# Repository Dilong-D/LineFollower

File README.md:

# LineFollower

Other materials used:

http://forbot.pl/blog/artykuly/podstawy/algorytm-linefollowera-c-poczatkujacych-id2722

http://forum.atnel.pl/topic7786.html

http://mikrokontroler.pl/page/3/?tag=kurs%20ATXmega

http://www.sunduino.pl/wordpress/xmega-adc-ogolnie-czesc-1/

https://extronic.pl/content/category/11-kurs-xmega

http://embedded-lab.com/blog/xmega-adc/

http://www.avrfreaks.net/forum/solved-xmega-all-adc-channels

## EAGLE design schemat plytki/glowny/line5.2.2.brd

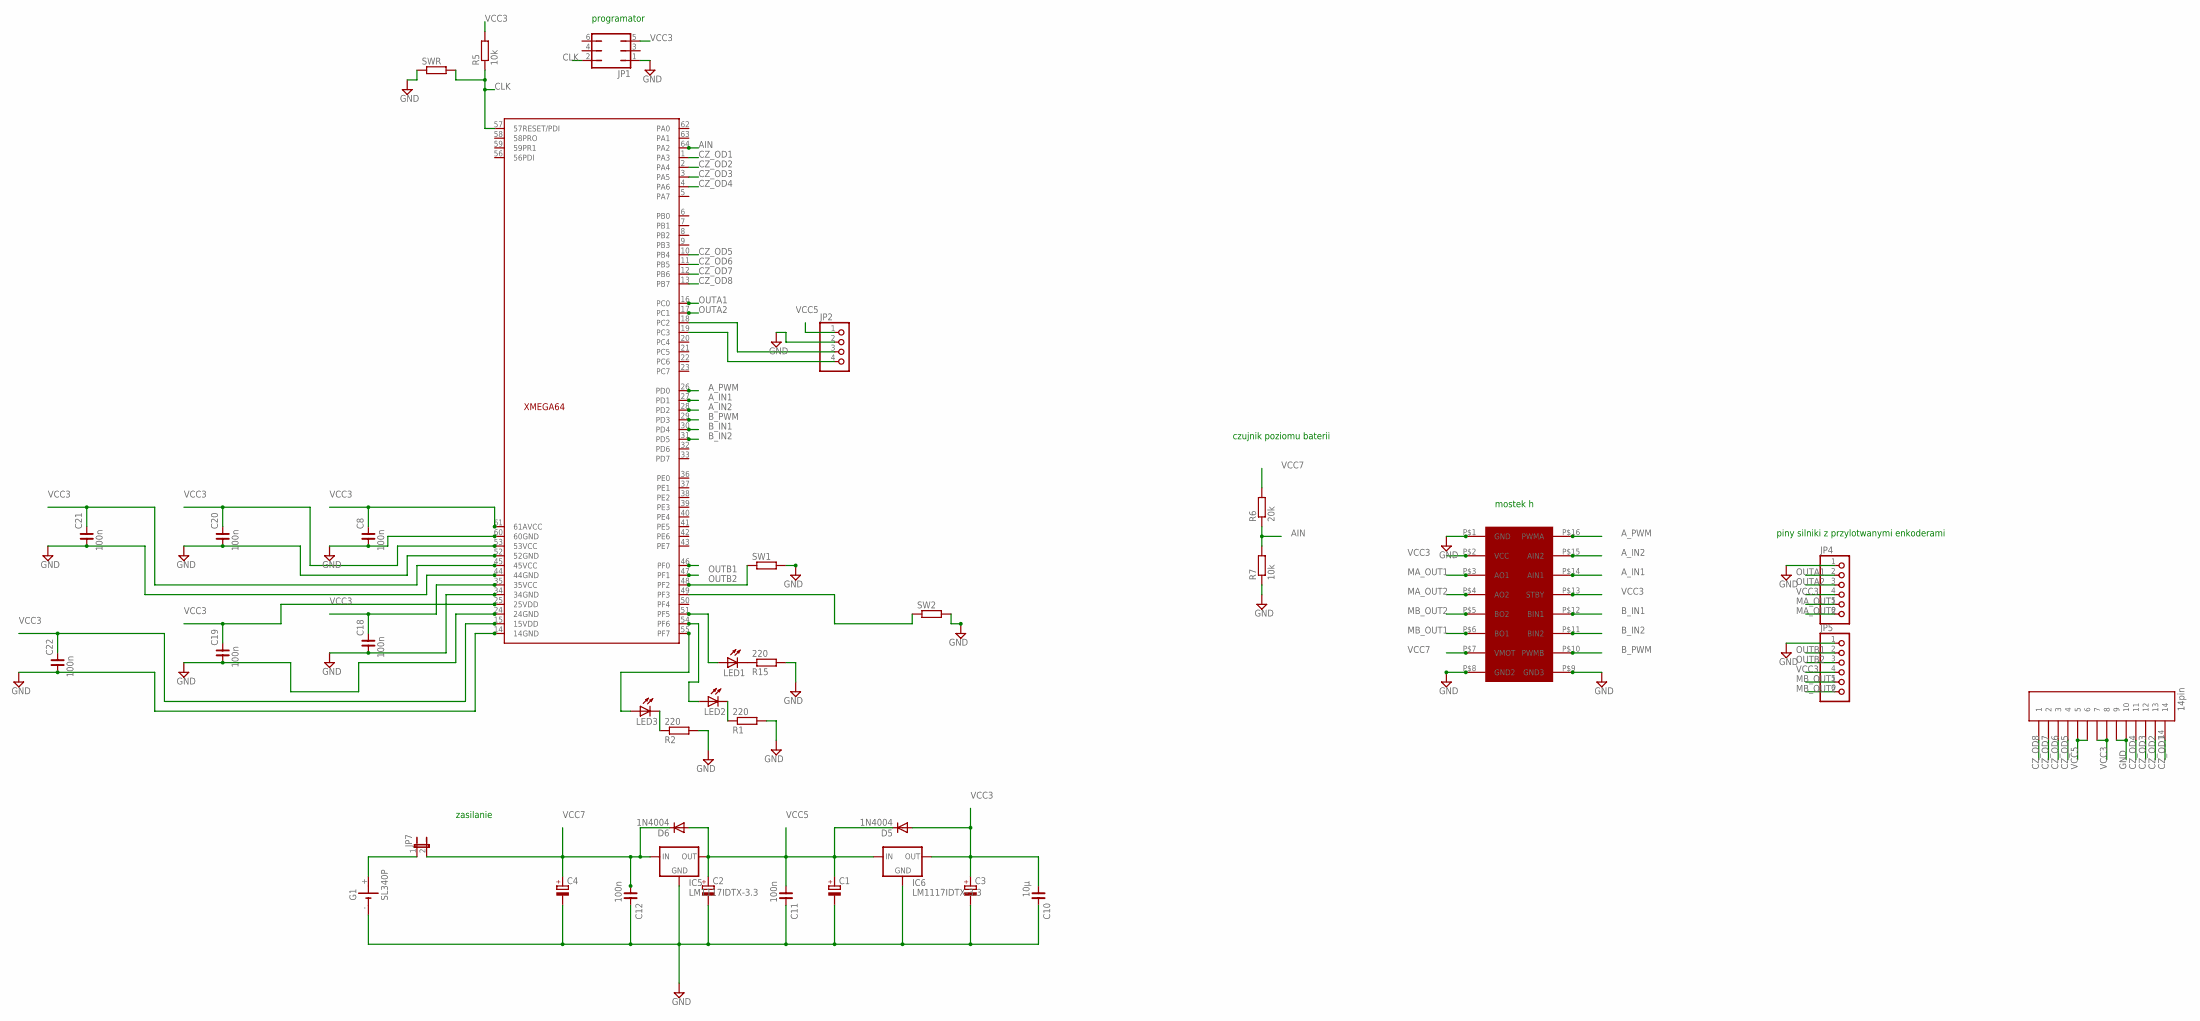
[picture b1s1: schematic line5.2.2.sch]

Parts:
C1, C2, C3, C4: CPOL-EU153CLV-0810; 153CLV-0810
C8, C11, C12, C18, C19, C20, C21, C22: 100n; C1206
C10: 10μ; C1206
D5, D6: 1N4004; DO41-10
G1: SL340P; SL-340/P3.6V
IC5, IC6: LM1117IDTX-3.3; TO252
JP1: JP3Q
JP2: PINHD-1X4; 1X04
JP4, JP5: PINHD-1X6; 1X06
JP7: JP1E; JP1
LED1, LED2, LED3: LEDSMT1206; 1206
R1, R2, R15: 220; R0805
R5, R7: 10k; R0805
R6: 20k; R0805
SW1, SW2: R-EU_R1206; R1206
SWR: R-EU_R1206; R1206
U$1: POLULU713
U$2: 14PIN
XMEGA64: XMEGA64C3TQFP64; TQFP64

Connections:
AIN: R6.1, R7.2, XMEGA64.64 (PA2)
A_IN1: U$1.P$14 (AIN1), XMEGA64.27 (PD1)
A_IN2: U$1.P$15 (AIN2), XMEGA64.28 (PD2)
A_PWM: U$1.P$16 (PWMA), XMEGA64.26 (PD0)
B_IN1: U$1.P$12 (BIN1), XMEGA64.30 (PD4)
B_IN2: U$1.P$11 (BIN2), XMEGA64.31 (PD5)
B_PWM: U$1.P$10 (PWMB), XMEGA64.29 (PD3)
CLK: JP1.2, R5.1, SWR.2, XMEGA64.57 (57RESET/PDI)
CZ_OD1: U$2.14, XMEGA64.1 (PA3)
CZ_OD2: U$2.13, XMEGA64.2 (PA4)
CZ_OD3: U$2.12, XMEGA64.3 (PA5)
CZ_OD4: U$2.11, XMEGA64.4 (PA6)
CZ_OD5: U$2.4, XMEGA64.10 (PB4)
CZ_OD6: U$2.3, XMEGA64.11 (PB5)
CZ_OD7: U$2.2, XMEGA64.12 (PB6)
CZ_OD8: U$2.1, XMEGA64.13 (PB7)
GND: C1.-, C2.-, C3.-, C4.-, C8.1, C10.2, C11.2, C12.2, C18.1, C19.1, C20.1, C21.1, C22.1, G1.-, IC5.1 (GND), IC6.1 (GND), JP1.1, JP2.2, JP4.1, JP5.1, R1.2, R2.2, R7.1, R15.2, SW1.2, SW2.2, SWR.1, U$1.P$1 (GND), U$1.P$8 (GND2), U$1.P$9 (GND3), U$2.9, U$2.10, XMEGA64.14 (14GND), XMEGA64.24 (24GND), XMEGA64.34 (34GND), XMEGA64.44 (44GND), XMEGA64.52 (52GND), XMEGA64.60 (60GND)
MA_OUT1: JP4.5, U$1.P$3 (AO1)
MA_OUT2: JP4.6, U$1.P$4 (AO2)
MB_OUT1: JP5.5, U$1.P$6 (BO1)
MB_OUT2: JP5.6, U$1.P$5 (BO2)
unnamed: LED1.A, XMEGA64.51 (PF5)
unnamed: SW2.1, XMEGA64.49 (PF3)
unnamed: JP2.4, XMEGA64.19 (PC3)
unnamed: JP2.3, XMEGA64.18 (PC2)
unnamed: LED2.C, R1.1
unnamed: LED2.A, XMEGA64.54 (PF6)
unnamed: LED3.C, R2.1
unnamed: LED3.A, XMEGA64.55 (PF7)
unnamed: G1.+, JP7.1
unnamed: LED1.C, R15.1
OUTA1: JP4.2, XMEGA64.16 (PC0)
OUTA2: JP4.3, XMEGA64.17 (PC1)
OUTB1: JP5.2, XMEGA64.46 (PF0)
OUTB2: JP5.3, XMEGA64.47 (PF1)
SW!: SW1.1, XMEGA64.48 (PF2)
VCC3: C3.+, C8.2, C10.1, C18.2, C19.2, C20.2, C21.2, C22.2, D5.A, IC6.TAB (OUT), JP1.5, JP4.4, JP5.4, R5.2, U$1.P$2 (VCC), U$1.P$13 (STBY), U$2.7, U$2.8, XMEGA64.15 (15VDD), XMEGA64.25 (25VDD), XMEGA64.35 (35VCC), XMEGA64.45 (45VCC), XMEGA64.53 (53VCC), XMEGA64.61 (61AVCC)
VCC5: C1.+, C2.+, C11.1, D5.C, D6.A, IC5.TAB (OUT), IC6.2 (IN), JP2.1, U$2.5, U$2.6
VCC7: C4.+, C12.1, D6.C, IC5.2 (IN), JP7.2, R6.2, U$1.P$7 (VMOT)

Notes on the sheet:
zasilanie
mostek h
piny silniki z przylotwanymi enkoderami
czujnik poziomu baterii
programator

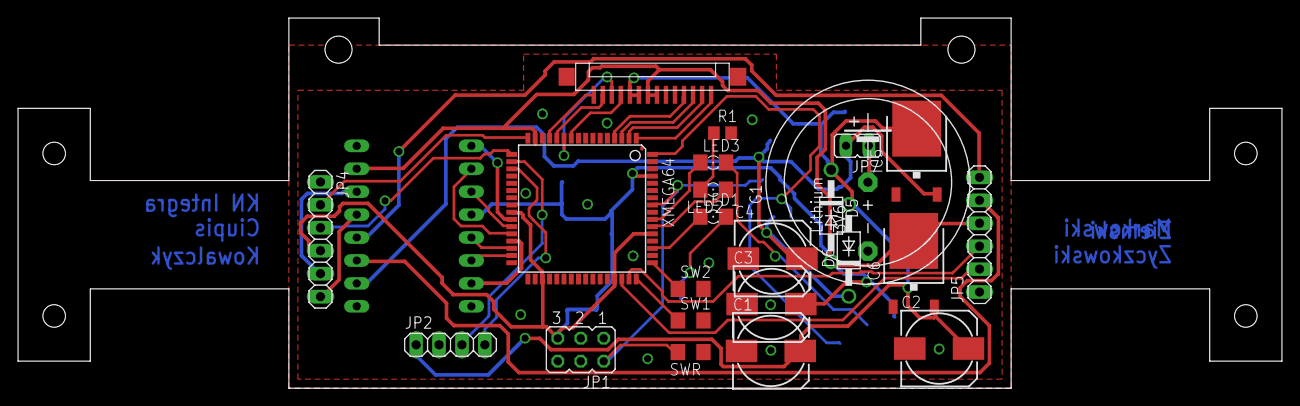
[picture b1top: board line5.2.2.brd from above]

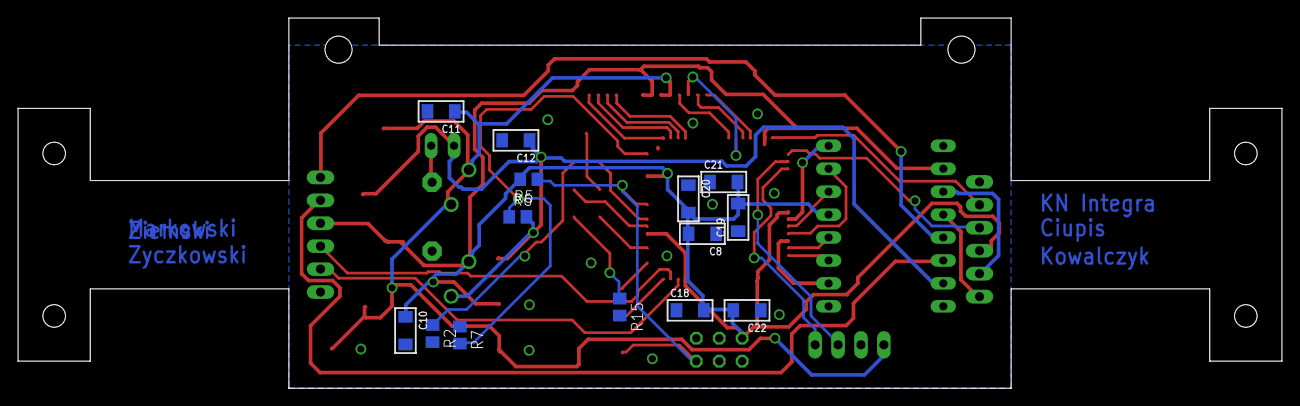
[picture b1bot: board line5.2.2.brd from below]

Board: 2 copper layers, 140.0 x 41.0 mm, 38 parts (14 on the bottom side), 39 nets.

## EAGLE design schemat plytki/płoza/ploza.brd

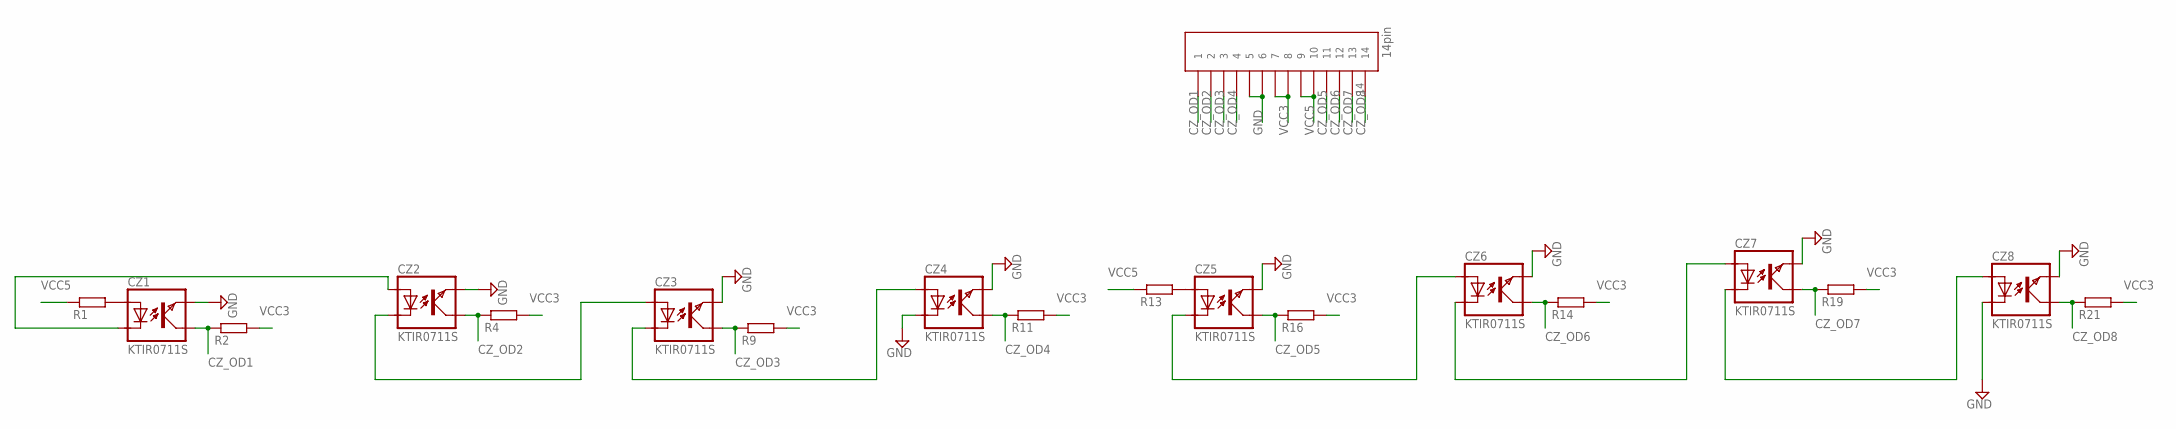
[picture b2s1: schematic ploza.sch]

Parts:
CZ1, CZ2, CZ3, CZ4, CZ5, CZ6, CZ7, CZ8: KTIR0711S; TOP
R1, R2, R4, R9, R11, R13, R14, R16, R19, R21: R-EU_R0805; R0805
U$2: 14PIN

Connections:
CZ_OD1: CZ1.KOLEKTOR, R2.1, U$2.1
CZ_OD2: CZ2.KOLEKTOR, R4.1, U$2.2
CZ_OD3: CZ3.KOLEKTOR, R9.1, U$2.3
CZ_OD4: CZ4.KOLEKTOR, R11.1, U$2.4
CZ_OD5: CZ5.KOLEKTOR, R16.1, U$2.11
CZ_OD6: CZ6.KOLEKTOR, R14.1, U$2.12
CZ_OD7: CZ7.KOLEKTOR, R19.1, U$2.13
CZ_OD8: CZ8.KOLEKTOR, R21.1, U$2.14
GND: CZ1.EMITER, CZ2.EMITER, CZ3.EMITER, CZ4.EMITER, CZ4.KATODA, CZ5.EMITER, CZ6.EMITER, CZ7.EMITER, CZ8.EMITER, CZ8.KATODA, U$2.5, U$2.6
unnamed: CZ5.KATODA, CZ6.ANODA
unnamed: CZ1.ANODA, R1.2
unnamed: CZ1.KATODA, CZ2.ANODA
unnamed: CZ2.KATODA, CZ3.ANODA
unnamed: CZ3.KATODA, CZ4.ANODA
unnamed: CZ5.ANODA, R13.2
unnamed: CZ6.KATODA, CZ7.ANODA
unnamed: CZ7.KATODA, CZ8.ANODA
VCC3: R2.2, R4.2, R9.2, R11.2, R14.2, R16.2, R19.2, R21.2, U$2.7, U$2.8
VCC5: R1.1, R13.1, U$2.9, U$2.10

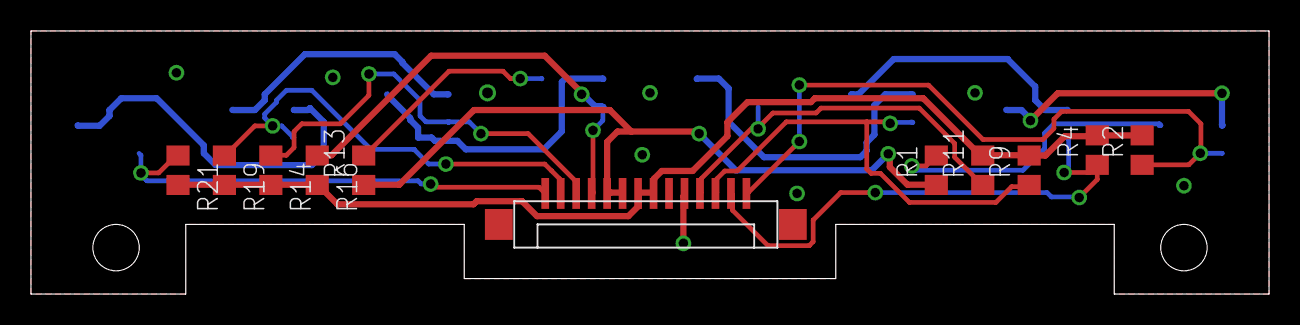
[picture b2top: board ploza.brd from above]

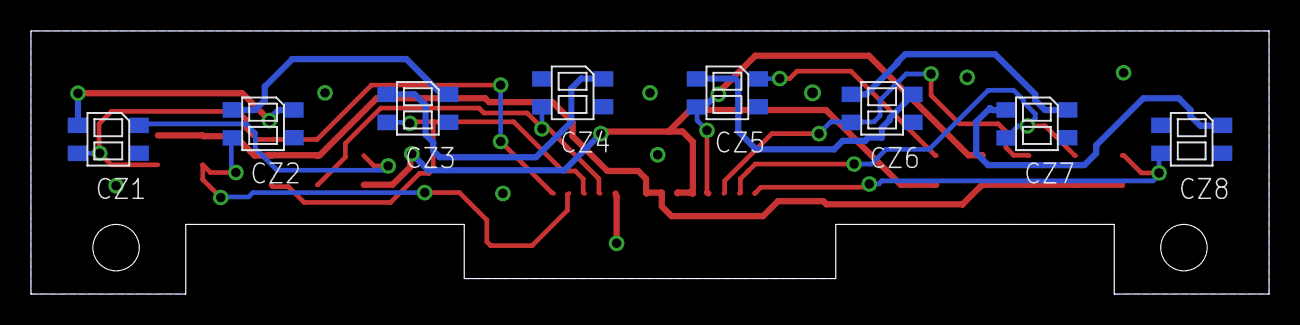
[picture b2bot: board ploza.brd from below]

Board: 2 copper layers, 80.0 x 17.0 mm, 19 parts (8 on the bottom side), 19 nets.

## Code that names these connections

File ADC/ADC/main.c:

/*
 * ADC.c
 *
 * Created: 2017-08-02 13:58:14
 * Author : Marcin
 */ 

#include <avr/io.h>
#include <avr/interrupt.h>
#include <util/delay.h>

volatile int czujnik[6]={0,0,0,0,0,0};
volatile int czujnik_int[6]={0,0,0,0,0,0};
volatile int prog=150;

int main(void)
{
	//IO configuration
	PORTA.DIR=~(PIN3_bm|PIN4_bm|PIN5_bm|PIN6_bm);						//Input from sensors
	PORTB.DIR=~(PIN4_bm|PIN5_bm|PIN6_bm|PIN7_bm);

	//Clock source configuration
	OscXtal();															//Configure clock signal

	//ADC
	//CLK.PSCTRL=CLK_PSADIV0_bm;										//Clock prescaler - no division
	ADCA.CTRLA=ADC_ENABLE_bm;											//ADCA - Enable
	ADCB.CTRLA=ADC_ENABLE_bm;											//ADCB - Enable
	ADCA.PRESCALER=ADC_PRESCALER2_bm;									//ADCA - Frequency devided by 64 (8MHz/64)
	ADCB.PRESCALER=ADC_PRESCALER2_bm;									//ADCB - Frequency devided by 64 (8MHz/64)
	ADCA.CTRLB=ADC_RESOLUTION_8BIT_gc|ADC_FREERUN_bm;					//ADCA - 8 bit resolution and freerun mode
	ADCB.CTRLB=ADC_RESOLUTION_8BIT_gc|ADC_FREERUN_bm;					//ADCB - 8 bit resolution and freerun mode
	ADCA.INTFLAGS=ADC_CH0IF_bm|ADC_CH1IF_bm|ADC_CH2IF_bm|ADC_CH3IF_bm;	//ADCA - Clear all interrupts
	ADCB.INTFLAGS=ADC_CH0IF_bm|ADC_CH1IF_bm|ADC_CH2IF_bm|ADC_CH3IF_bm;	//ADCB - Clear all interrupts
	ADCA.EVCTRL=ADC_SWEEP_0123_gc;										//ADCA - Channels 0, 1, 2, 3 in freerun mode
	ADCB.EVCTRL=ADC_SWEEP_0123_gc;										//ADCB - Channels 0, 1, 2, 3 in freerun mode
	ADCA.CH0.CTRL=ADC_CH_INPUTMODE_SINGLEENDED_gc;						//ADCA.CH0 - Single-ended mode
	ADCA.CH1.CTRL=ADC_CH_INPUTMODE_SINGLEENDED_gc;						//ADCA.CH1 - Single-ended mode
	ADCA.CH2.CTRL=ADC_CH_INPUTMODE_SINGLEENDED_gc;						//ADCA.CH2 - Single-ended mode
	ADCA.CH3.CTRL=ADC_CH_INPUTMODE_SINGLEENDED_gc;						//ADCA.CH3 - Single-ended mode
	ADCB.CH0.CTRL=ADC_CH_INPUTMODE_SINGLEENDED_gc;						//ADCB.CH0 - Single-ended mode
	ADCB.CH1.CTRL=ADC_CH_INPUTMODE_SINGLEENDED_gc;						//ADCB.CH1 - Single-ended mode
	ADCB.CH2.CTRL=ADC_CH_INPUTMODE_SINGLEENDED_gc;						//ADCB.CH2 - Single-ended mode
	ADCB.CH3.CTRL=ADC_CH_INPUTMODE_SINGLEENDED_gc;						//ADCB.CH3 - Single-ended mode
	ADCA.CH0.INTCTRL=ADC_CH_INTLVL0_bm;									//ADCA.CH0 - Low priority interrupt when conversion complete
	ADCA.CH1.INTCTRL=ADC_CH_INTLVL0_bm;									//ADCA.CH1 - Low priority interrupt when conversion complete
	ADCA.CH2.INTCTRL=ADC_CH_INTLVL0_bm;									//ADCA.CH2 - Low priority interrupt when conversion complete
	ADCA.CH3.INTCTRL=ADC_CH_INTLVL0_bm;									//ADCA.CH3 - Low priority interrupt when conversion complete
	ADCB.CH0.INTCTRL=ADC_CH_INTLVL0_bm;									//ADCB.CH0 - Low priority interrupt when conversion complete
	ADCB.CH1.INTCTRL=ADC_CH_INTLVL0_bm;									//ADCB.CH1 - Low priority interrupt when conversion complete
	ADCB.CH2.INTCTRL=ADC_CH_INTLVL0_bm;									//ADCB.CH2 - Low priority interrupt when conversion complete
	ADCB.CH3.INTCTRL=ADC_CH_INTLVL0_bm;									//ADCB.CH3 - Low priority interrupt when conversion complete
	ADCA.CH0.MUXCTRL=ADC_CH_MUXPOS_PIN3_gc;								//ADCA.CH0 - Connect to PA3
	ADCA.CH1.MUXCTRL=ADC_CH_MUXPOS_PIN4_gc;								//ADCA.CH1 - Connect to PA4
	ADCA.CH2.MUXCTRL=ADC_CH_MUXPOS_PIN5_gc;								//ADCA.CH2 - Connect to PA5
	ADCA.CH3.MUXCTRL=ADC_CH_MUXPOS_PIN6_gc;								//ADCA.CH3 - Connect to PA6
	ADCB.CH0.MUXCTRL=ADC_CH_MUXPOS_PIN4_gc;								//ADCB.CH0 - Connect to PB4
	ADCB.CH1.MUXCTRL=ADC_CH_MUXPOS_PIN5_gc;								//ADCB.CH1 - Connect to PB5
	ADCB.CH2.MUXCTRL=ADC_CH_MUXPOS_PIN6_gc;								//ADCB.CH2 - Connect to PB6
	ADCB.CH3.MUXCTRL=ADC_CH_MUXPOS_PIN7_gc;								//ADCB.CH3 - Connect to PB7
	ADCB.CH0.CTRL|=ADC_CH_START_bm;										//Start conversion
	//Comments to ADC:
	//We need to control ADCB.CH0-3.MUXCTRL(=ADC_CH_MUXPOS_PINx_gc;)
	//ADCB.CHx.RESL is result of conversion
	//ADCB.CHx.CTRL|=ADC_CH_START_bm; start conversion on channel (not in free-run)
	
	//Enable interrupts
	PMIC.CTRL=PMIC_LOLVLEN_bm;											//Enable low level interrupts
	sei();																//Enable all interrupts

	//Main loop
    while (1)
    {
		//Here results should be sent over BT to check correctness.
    }
}

ISR(ADCA_CH0_vect)														//ADCA.CH0 - Interrupt
{
	czujnik_int[0]=ADCA.CH0.RESL;
	czujnik[0]=(czujnik_int[0]>prog);									//Check whether is above line
}

ISR(ADCA_CH1_vect)														//ADCA.CH1 - Interrupt
{
	czujnik_int[1]=ADCA.CH0.RESL;
	czujnik[1]=(czujnik_int[1]>prog);									//Check whether is above line
}

ISR(ADCA_CH2_vect)														//ADCA.CH2 - Interrupt
{
	czujnik_int[2]=ADCA.CH0.RESL;
	czujnik[2]=(czujnik_int[2]>prog);									//Check whether is above line
}

ISR(ADCA_CH3_vect)														//ADCA.CH3 - Interrupt
{
	czujnik_int[3]=ADCA.CH0.RESL;
	czujnik[3]=(czujnik_int[3]>prog);									//Check whether is above line
}

ISR(ADCB_CH0_vect)														//ADCB.CH0 - Interrupt
{
	czujnik_int[4]=ADCA.CH0.RESL;
	czujnik[4]=(czujnik_int[4]>prog);									//Check whether is above line
}

ISR(ADCB_CH1_vect)														//ADCB.CH1 - Interrupt
{
	czujnik_int[5]=ADCA.CH0.RESL;
	czujnik[5]=(czujnik_int[5]>prog);									//Check whether is above line
}

ISR(ADCB_CH2_vect)														//ADCB.CH2 - Interrupt
{
	czujnik_int[6]=ADCA.CH0.RESL;
	czujnik[6]=(czujnik_int[6]>prog);									//Check whether is above line
}

ISR(ADCB_CH3_vect)														//ADCB.CH3 - Interrupt
{
	czujnik_int[7]=ADCA.CH0.RESL;
	czujnik[7]=(czujnik_int[7]>prog);									//Check whether is above line
}

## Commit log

2017-07-21 second commit
2017-07-21 Konfiguracja bluetooth, diod led, przyciskow, timerow i ich przerwan, PWM na koła, enkoderow
2017-07-23 Konfiguracja bluetooth, diod led, przyciskow, timerow i ich przerwan, PWM na koła, enkoderow, uaktualnionna lista portow w main.c
2017-08-03 ADC code
2017-08-03 Materials

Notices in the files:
parts and their libraries:
rc-master-smd: Copyright (C) 2007, Bob Starr
